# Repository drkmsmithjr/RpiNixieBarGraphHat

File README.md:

# Nixie Bar Graph Hat for Raspberry Pi Zero (updated to Part 2)

This project as described in [www.surfncircuits.com](https://wp.me/p85ddV-HQ) came about because I needed a retro looking linear meter for my espresso maker water tank. I’m always running out of water in my espresso maker, and a cool display letting me know how much water is left and to let me know when to fill it up is definitely needed. In this project, I’ll create a HAT for the Raspberry Pi that can drive two IN-9 or IN-13 linear Nixie tubes. While I’m using this HAT as a single water meter display, this same linear display would be great for showing temperature, bar graphs, audio VU meters, even surf heights by days of the week. The [Nixie Tube Power Supply](https://wp.me/p85ddV-Ck), designed in an earlier blog will work perfectly to drive up to four of the IN-13 Nixie tubes or one IN-9 Nixie tube.

This github repository contains the Kicad Schematic, Layout, and Python Library for a PCB Hat that works with the Rasperry Pi Zero, and B+ along with the [Nixie Tube Power Supply](https://wp.me/p85ddV-Ck).  

__KC_NixieBarGraphHat__:  Kicad schematic, PCB layout, [BOM](https://github.com/drkmsmithjr/RpiNixieBarGraphHat/blob/master/KC_NixieBargraphHat/NixieBargraphHat.ods) of the HAT.  The footprint is designed to mounted to the top of the Raspberry Pin zero and B+.   The board is orderable at <a href="https://oshpark.com/shared_projects/Tt69yaPK"></img></a>

__PythonRpiIN9Nixie__:  The Python Library that can control and the Nixie Bar Graph Hat.   Please see the README file in this submodule and the Blog Entry at [surfncircuits](http://www.surfncircuits.com) for details on how to install the library and how it runs.  

__Datasheeets__: Datasheets for the different components on the pCB.   Many of the datasheets are also linked directly in the Kicad schematic to the Digikey (TM) datasheet.    

See other reference blogs entry at  www.surfncircuits.com:
  * [KiCad Power Tools Help Shrink The Nixie Tube Power Supply (part 3)](https://wp.me/p85ddV-Ck)

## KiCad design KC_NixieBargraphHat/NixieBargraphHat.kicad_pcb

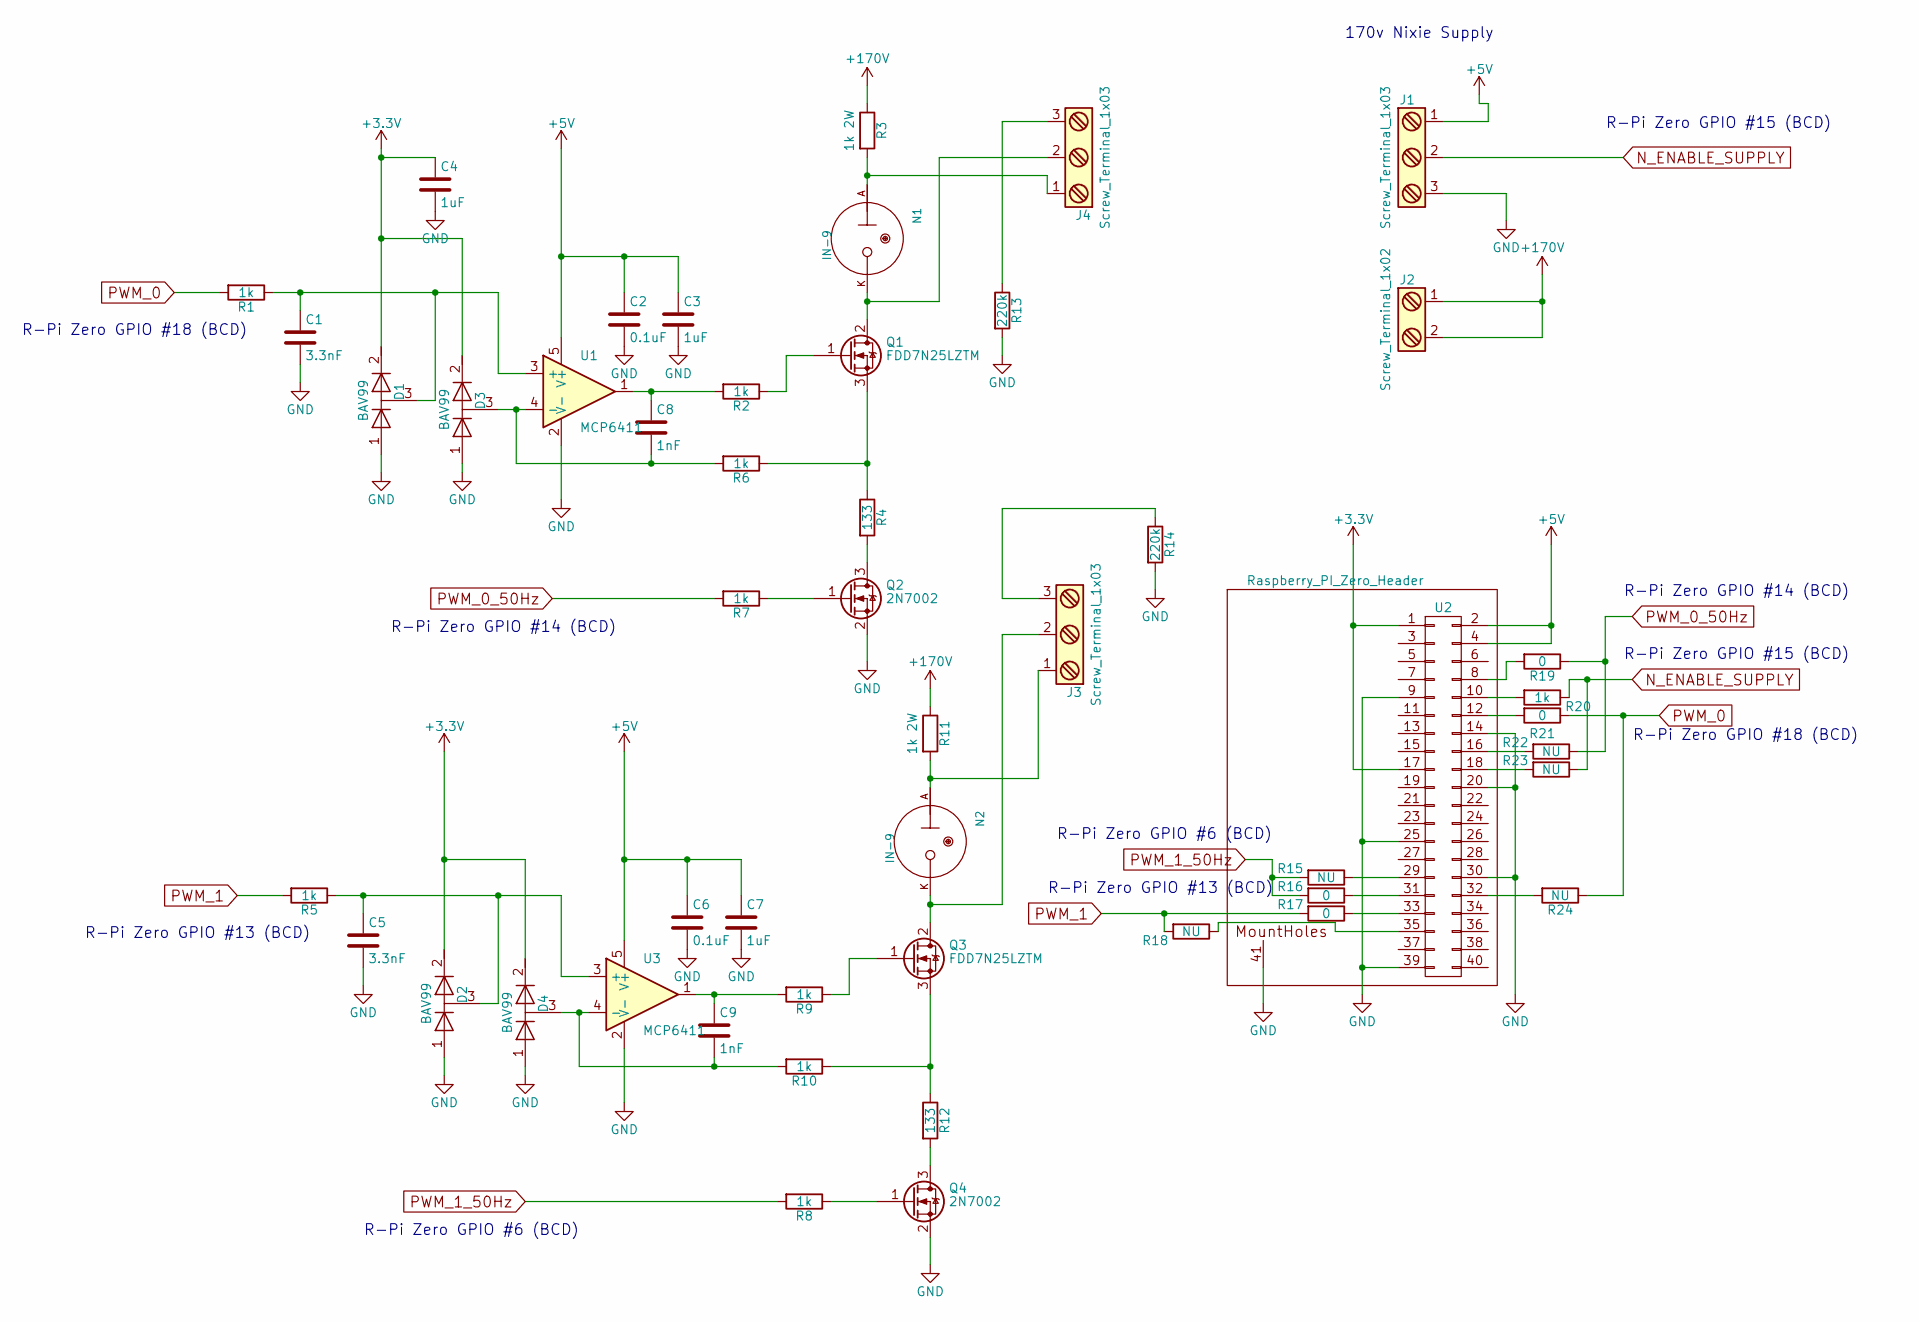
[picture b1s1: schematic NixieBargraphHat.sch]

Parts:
C1, C5: 3.3nF; C_0805_HandSoldering; MPN C0805C332KDRACAUTO
C2, C6: 0.1uF; C_0805_HandSoldering; MPN C0805C104K3RACTU
C3, C4, C7: 1uF; C_0805_HandSoldering; MPN CL21F105ZBFNNNE
C8, C9: 1nF; C_0805_HandSoldering; MPN C0805C102J5HACAUTO
D1, D2, D3, D4: BAV99; SOT-23; MPN BAV99,235
J1, J3, J4: Screw_Terminal_1x03; TerminalBlock_Phoenix_MPT-2.54mm_3pol; MPN 1725669
J2: Screw_Terminal_1x02; TerminalBlock_Phoenix_MPT-2.54mm_2pol; MPN 1725656
N1, N2: IN-9
Q1, Q3: FDD7N25LZTM; TO-252-2Lead; MPN FDD7N25LZTM
Q2, Q4: 2N7002; SOT-23; MPN 2N7002-TP
R1, R5, R6, R7, R8, R10: 1k; R_0805_HandSoldering; MPN RC0805FR-071KL
R2, R9: 1k; R_0805_HandSoldering; MPN RC0805FR-078K2L
R3, R11: 1k 2W; R_Axial_DIN0411_L9.9mm_D3.6mm_P12.70mm_Horizontal; MPN PR02000201001JR500
R4, R12: 133; R_0805_HandSoldering; MPN RC0805FR-07133RL
R13, R14: 220k; R_0805_HandSoldering; MPN CRGCQ0805F220K
R15, R18, R22, R23, R24: NU; R_0805_HandSoldering
R16, R17, R19, R21: 0; R_0805_HandSoldering
R20: 1k; R_0805_HandSoldering
U1, U3: MCP6411; SOT-23-5_HandSoldering; MPN MCP6411T-E/OT
U2: Raspberry_PI_Zero_Header; Raspberry_Pi_Zero_40pins

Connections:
+3V3: C4.1, D1.2 (K), D2.2 (K), D3.2 (K), D4.2 (K), U2.1, U2.17
+5V: C2.1, C3.1, C6.1, C7.1, J1.1, U1.5 (V+), U2.2, U2.4, U3.5 (V+)
+170V: J2.1, J2.2, R3.1, R11.1
GND: C1.2, C2.2, C3.2, C4.2, C5.2, C6.2, C7.2, D1.1 (A), D2.1 (A), D3.1 (A), D4.1 (A), J1.3, Q2.2 (S), Q4.2 (S), R13.2, R14.2, U1.2 (V-), U2.9, U2.14, U2.20, U2.25, U2.30, U2.39, U2.41 (MountHoles), U3.2 (V-)
N_ENABLE_SUPPLY: J1.2, R20.1, R23.1
unnamed: C1.1, D1.3 (common), R1.1, U1.3 (+)
unnamed: C5.1, D2.3 (common), R5.1, U3.3 (+)
unnamed: C8.1, R2.2, U1.1
unnamed: C8.2, D3.3 (common), R6.2, U1.4 (-)
unnamed: C9.1, R9.2, U3.1
unnamed: C9.2, D4.3 (common), R10.2, U3.4 (-)
unnamed: J3.1, N2.A, R11.2
unnamed: J3.2, N2.K, Q3.2 (D)
unnamed: J3.3, R14.1
unnamed: J4.1, N1.A, R3.2
unnamed: J4.2, N1.K, Q1.2 (D)
unnamed: J4.3, R13.1
unnamed: Q1.1 (G), R2.1
unnamed: Q1.3 (S), R4.1, R6.1
unnamed: Q2.1 (G), R7.1
unnamed: Q2.3 (D), R4.2
unnamed: Q3.1 (G), R9.1
unnamed: Q3.3 (S), R10.1, R12.1
unnamed: Q4.1 (G), R8.1
unnamed: Q4.3 (D), R12.2
unnamed: R15.1, U2.29
unnamed: R16.1, U2.31
unnamed: R17.1, U2.33
unnamed: R18.1, U2.35
unnamed: R19.2, U2.8
unnamed: R20.2, U2.10
unnamed: R21.2, U2.12
unnamed: R22.2, U2.16
unnamed: R23.2, U2.18
unnamed: R24.2, U2.32
PWM_0: R1.2, R21.1, R24.1
PWM_0_50Hz: R7.2, R19.1, R22.1
PWM_1: R5.2, R17.2, R18.2
PWM_1_50Hz: R8.2, R15.2, R16.2

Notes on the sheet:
R-Pi Zero GPIO #18 (BCD)
R-Pi Zero GPIO #14 (BCD)
R-Pi Zero GPIO #15 (BCD)
170v Nixie Supply
R-Pi Zero GPIO #13 (BCD)
R-Pi Zero GPIO #6 (BCD)

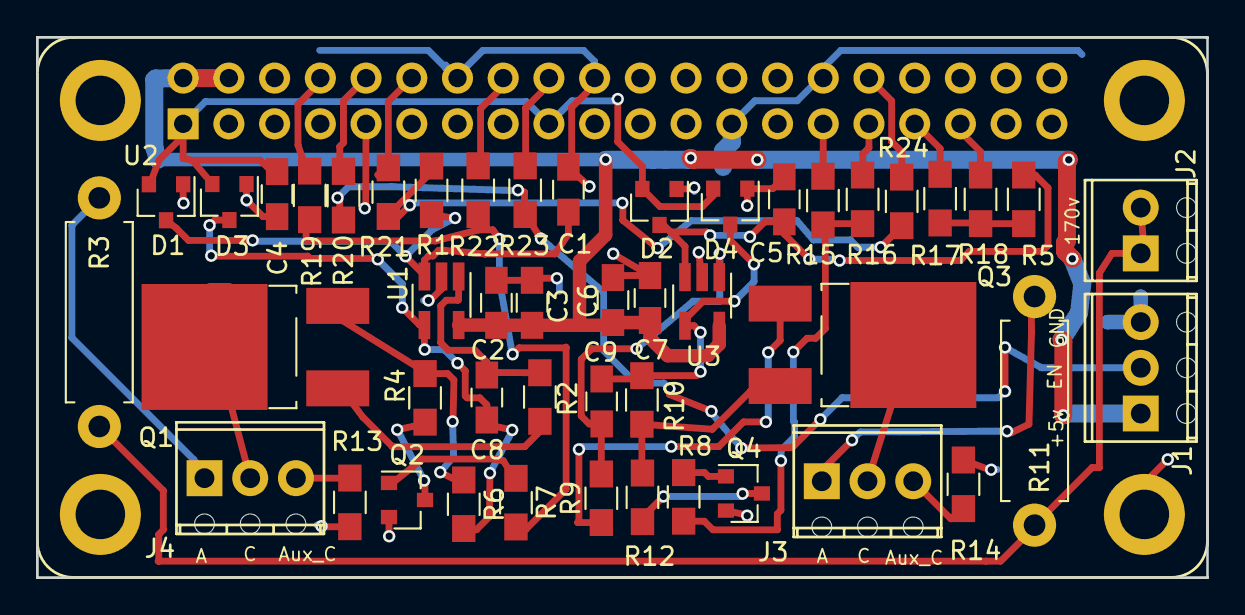
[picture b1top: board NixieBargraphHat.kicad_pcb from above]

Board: 2 copper layers, 65.0 x 30.0 mm, 48 parts (0 on the bottom side), 39 nets.

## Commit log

2019-01-07 Initial entry of the IN-9 Hat for the Raspbarry Pi Zero
2019-01-07 added the PythonRpiIN9Nixie submodule to this repository.
2019-01-13 Added connectors for the power supply and the Raspberry Pi header
2019-01-13 updated the submodule
2019-01-13 Uploaded project image
2019-01-13 removed image
2019-01-13 ploted the schematic and added a readme file along with a license file
2019-01-13 READM
2019-01-13 README
2019-01-14 Adjusted the schematic to have two channels for the Left and Right Nixie. Also adjusted the PWM to have hardware PWM for the cathod signals, but the low frequency dimming will be done with the 50 Hz 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
2019-01-14 updated the submodules
2019-01-17 updated the schematic to include a feedback for op-amp to avoid oscillation
2019-01-26 updated the schematic with dual solution for left and right channels
2019-01-26 updated with new README file to reference the new schematic
2019-02-16 updated layout files.
2019-02-16 updated submodule to latest
2019-02-16 updated submodule python code
2019-02-16 added gerber files
2019-02-16 added links to the surfncircuits blog
2019-02-18 Updated the BOM to a different FET that is in stock 250v
2019-02-18 added datasheet of new FET
2019-02-18 Added a 3d Image to readme file
2019-02-18 corrected file name
2019-03-18 adjusted the gate resistor for increased bandwidth
2019-04-07 Updated the follwoing changes: 1. Adjusted the gate resistor BOM to include a 1kohm resistor to gate of mosfet 2. updated silk screen to add labels for each of the Nixie tube and power supply connect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
2019-04-07 updated the BOM to add the changes R2 and R9
2019-04-07 update BOM to add 1k to enable pin
2019-09-29 Added all the changes for Part 2 of the Hat. UPdated silksceen, reduced R2 and R9, new gerbers (Part 2). The original gerbers were saved.
2019-09-29 Update README.md
    Updated to part 2
2019-09-29 added new schematic picture
2019-09-29 moved the schematic and 3d images files
2019-09-29 Update README.md
    fixed the file link for the schematic
2019-09-29 updated the schematic file
2019-09-29 updated the schematic
2019-09-29 Update README.md
    updated with lin
2019-09-29 Update README.md
    Added link to the BOM open libre file format.
2019-09-29 Update README.md
    Added a small description
2019-09-29 Update README.md
    Added image picture of the project
2019-09-29 added a new image of the system setup.
